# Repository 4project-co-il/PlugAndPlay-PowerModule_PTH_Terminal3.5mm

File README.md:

# PlugAndPlay: Power Module with 3.5mm PTH Terminal Block
This is the repository with the files for Power Module for the PlugAndPlay boards.

That module is equiped with 3.5mm PTH Terminal Block and is rated for up to 10A of current.
The PCB and connections of the power modules on PlugAndPlay devices are designed to pass up to 10A, although wasn't tested.

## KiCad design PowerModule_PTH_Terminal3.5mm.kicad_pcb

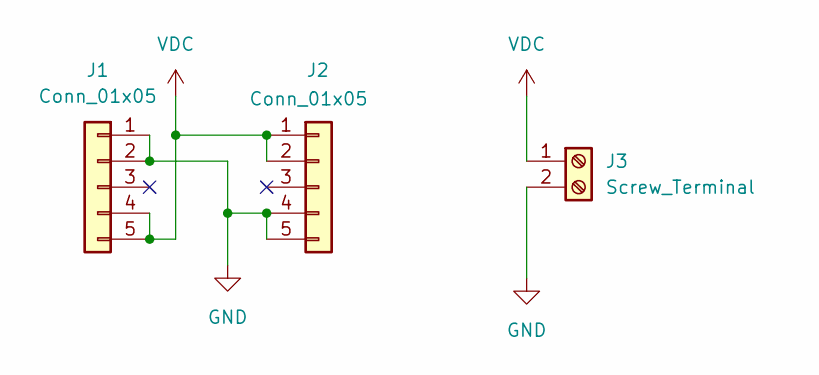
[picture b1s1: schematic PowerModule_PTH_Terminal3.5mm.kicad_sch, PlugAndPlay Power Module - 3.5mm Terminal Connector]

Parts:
J1: Conn_01x05; PinSocket_1x05_P2.54mm_Vertical_SMD_Pin1Right; MPN RealRun
J2: Conn_01x05; PinSocket_1x05_P2.54mm_Vertical_SMD_Pin1Left; MPN RealRun
J3: Screw_Terminal; TerminalBlock_4Ucon_1x02_P3.50mm_Horizontal; MPN C695629

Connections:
GND: J1.1, J1.2, J2.4, J2.5, J3.2
VDC: J1.4, J1.5, J2.1, J2.2, J3.1

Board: 2 copper layers, 3 parts (1 on the bottom side), 2 nets, no tracks yet.

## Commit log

2025-04-27 Fix the wrong side connectors
